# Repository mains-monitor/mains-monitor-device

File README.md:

# Mains Monitor

The device monitors a presence of mains voltage and sends notifications to the Backend when it turns on or off.
It uses ESP32-C3 MCU as a core component. It implements the logic of the device and connects it to the outer world via Wi-Fi.

The device powers from 5V DC via micro-USB connector and from 3.7V 1000 mAh Li-Po battery, when mains is not available.
Most of the time the device stays in deep sleep mode, so it consumes micro Amps. It wakes up for 20 sec when 5V DC power source becomes available or turns off just for sending a notification to the Backend, then goes to deep sleep again. Peak power consumption when device is transmitting data via Wi-Fi is 500 mA.

# First launch configuration

When device starts the first time it creates a Wi-Fi hotspot network with SSID ``MD_<CHIPID>``. The password is ``md123456``.
Connect to it from a smartphone. After that it will open a configuration portal powered by WiFiManager Arduino library. It allows you to select a home Wi-Fi network the device will be connected to and a DTEK group number. The DTEK group number will be used later on the Backend.

# Folders & files description

* ``cad/`` - FreeCAD project and *.STL files of the enclosure for 3D printing
* ``libs/`` - KiCAD library files (schematic symbols and footprints)
* ``production/`` - Gerber, component placement files and Bill Of Materials for PCB production on the factory (for example, JLCPCB)
* ``firmware/`` - firmware sources for ESP32-C3 MCU, the heart of Mains Monitor

# Schematic

## PCB design

See [PDF file](doc/pcb-design.pdf) or ``./mains-detector.kicad_pcb`` filer in KiCAD format.

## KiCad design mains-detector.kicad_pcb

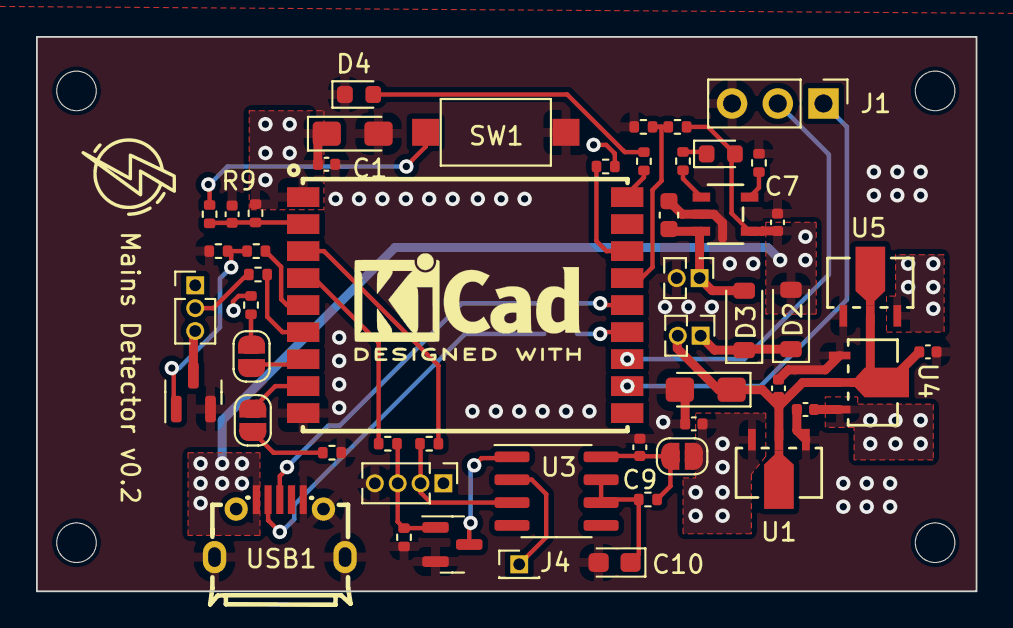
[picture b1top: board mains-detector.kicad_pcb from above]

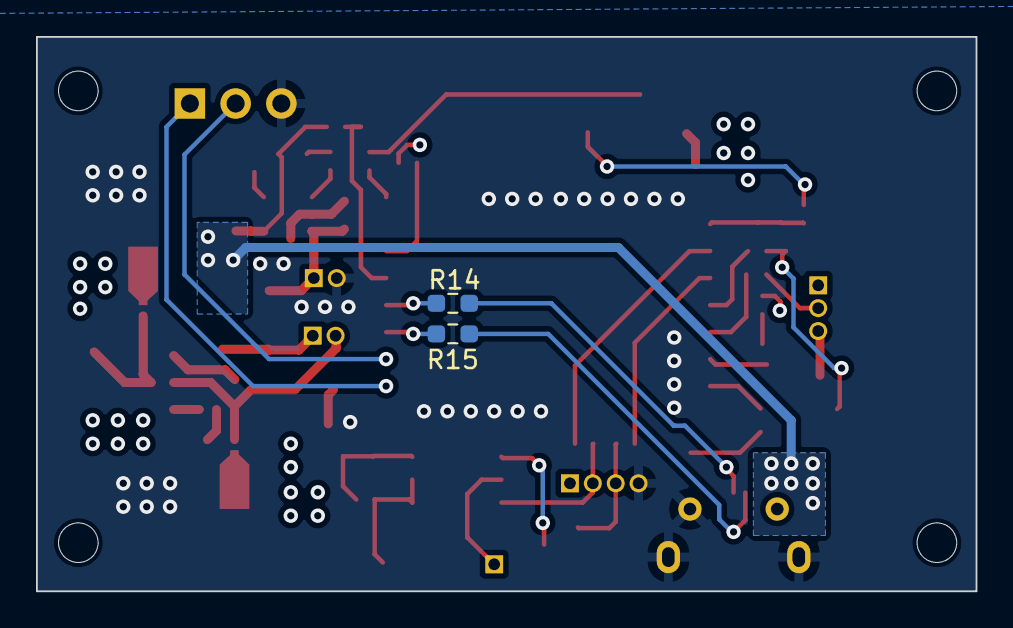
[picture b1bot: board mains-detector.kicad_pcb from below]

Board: 4 copper layers, 52.2 x 30.8 mm, 58 parts (2 on the bottom side), 38 nets.

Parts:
BT1: Li-Po 3.7V; PinHeader_1x02_P1.27mm_Vertical
C1, C9: 0.1u; C_0402_1005Metric
C2, C4: 10u; CP_EIA-3216-10_Kemet-I_Pad1.58x1.35mm_HandSolder
C3: 100n; C_0402_1005Metric
C5, C6, C7, C11, C12: 1u; C_0402_1005Metric
C8: 10u; C_0603_1608Metric
C10: 4.7u; CP_EIA-2012-12_Kemet-R
D1: LED-Blue; LED_0603_1608Metric
D2, D3: MBR0520LT1; D_SOD-123
D4: STATUS; LED_0603_1608Metric
H1, H2, H3, H4: MountingHole; MountingHole_2.2mm_M2
J1: UART; PinHeader_1x03_P2.54mm_Vertical
J2: FS1000A; PinHeader_1x03_P1.27mm_Vertical
J3: GPIOS; PinHeader_1x04_P1.27mm_Vertical
J4: ANT; PinHeader_1x01_P1.27mm_Vertical
JP1, JP2, JP3: SolderJumper_2_Open; SolderJumper-2_P1.3mm_Open_RoundedPad1.0x1.5mm
L1: ESP-C3-13U-4M; WIRELM-SMD_ESP-C3-13U-2M
Q1, Q2: IRLML2402; SOT-23
R1, R2, R3, R7, R9: 10k; R_0402_1005Metric
R4, R8: 3k; R_0402_1005Metric
R5, R6: 5k; R_0402_1005Metric
R10, R11, R12, R18, R19: 100; R_0402_1005Metric
R13, R16, R17: 100k; R_0402_1005Metric
R14, R15: 22; R_0603_1608Metric_Pad0.98x0.95mm_HandSolder
SW1: RESET; SW_SPST_CK_RS282G05A3
SW2: ONOFF; PinHeader_1x02_P1.27mm_Vertical
U1, U4, U5: XC6206P332PR-G; SOT-89_TOR
U2: TP4065-4.2V-SOT25-R; SOT-23-5L_TPW
U3: NE555D; SOIC-8_3.9x4.9mm_P1.27mm
USB1: MICROXNJ; MICRO-USB-SMD_MICROXNJ

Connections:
D+: L1.14 (IO19), R14.2
D-: L1.13 (IO18), R15.2
EN: C3.1, L1.2 (EN), R9.2, R10.1
GND: BT1.2 (-), C1.1, C2.2, C3.2, C4.2, C5.2, C6.2, C7.2, C8.2, C9.1, C10.2, C11.2, C12.2, D4.1 (K), J1.3, J3.4, L1.9 (GND), Q1.2 (S), Q2.2 (S), R2.2, R5.2, R7.2, R13.1, R16.1, SW1.1, U1.1 (VSS), U2.2 (GND), U4.1 (VSS), U5.1 (VSS), USB1.5 (GND), USB1.6 (SH1), USB1.7 (SH2), USB1.8 (SH3), USB1.9 (SH4)
IO4: J3.2, R18.1, U3.3 (Q)
IO5: J3.3, Q1.1 (G), R16.2, R19.1
unnamed: BT1.1 (+), C8.1, D3.2 (A), U2.3 (BAT)
unnamed: D1.1 (K), R4.2
unnamed: D2.1 (K), D3.1 (K), SW2.1 (A)
unnamed: D4.2 (A), R8.1
unnamed: J1.1, L1.11 (RXD)
unnamed: J1.2, L1.12 (TXD)
unnamed: J2.2, R11.2
unnamed: J2.3, Q2.3 (D)
unnamed: J4.1, U3.2 (TR)
unnamed: JP1.1 (A), R3.2
unnamed: JP1.2 (B), L1.7 (IO8)
unnamed: JP2.1 (A), R2.1
unnamed: JP2.2 (B), L1.8 (IO9)
unnamed: C9.2, JP3.1 (A), R17.2, U3.8 (VCC)
unnamed: L1.18 (IO0), R8.2
unnamed: L1.16 (IO2), R1.2
unnamed: L1.3 (IO4), R18.2
unnamed: L1.4 (IO5), R19.2
unnamed: Q1.3 (D), U3.1 (GND)
unnamed: Q2.1 (G), R12.2, R13.2
unnamed: R10.2, SW1.2
unnamed: C4.1, C5.1, C11.1, SW2.2 (B), U1.2 (VIN), U4.2 (VIN), U5.2 (VIN)
unnamed: R4.1, U2.1 (CHRG)
unnamed: R5.1, U2.5 (PROG)
unnamed: C10.1, R17.1, U3.6 (THR), U3.7 (DIS)
unnamed: R14.1, USB1.3 (D+)
unnamed: R15.1, USB1.2 (D-)
SENSE: L1.15 (IO3), R6.2, R7.1
TX: L1.6 (IO7), R11.1
TX_EN: L1.5 (IO6), R12.1
VBUS: C7.1, D1.2 (A), D2.2 (A), R6.1, U2.4 (VCC), USB1.1 (VBUS)
VCC: C1.2, C2.1, C6.1, C12.1, J2.1, J3.1, JP3.2 (B), L1.1 (VCC), R1.1, R3.1, R9.1, U1.3 (VOUT), U4.3 (VOUT), U5.3 (VOUT)

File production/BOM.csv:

"Comment","Designator","Footprint","LCSC"
"0.1u","C1,C9","Capacitor_SMD:C_0402_1005Metric","C307331"
"10u","C2,C4","Capacitor_Tantalum_SMD:CP_EIA-3216-10_Kemet-I_Pad1.58x1.35mm_HandSolder","C7171"
"100n","C3","Capacitor_SMD:C_0402_1005Metric","C307331"
"1u","C5,C6,C7,C11,C12","Capacitor_SMD:C_0402_1005Metric","C52923"
"10u","C8","Capacitor_SMD:C_0603_1608Metric","C96446"
"4.7u","C10","Capacitor_Tantalum_SMD:CP_EIA-2012-12_Kemet-R","C2158112"
"LED-Blue","D1","LED_SMD:LED_0603_1608Metric","C2286"
"MBR0520LT1","D2,D3","Diode_SMD:D_SOD-123","C8598"
"STATUS","D4","LED_SMD:LED_0603_1608Metric","C2290"
"IRLML2402","Q1,Q2","Package_TO_SOT_SMD:SOT-23","C20917"
"10k","R1,R2,R3,R7,R9","Resistor_SMD:R_0402_1005Metric","C25744"
"3k","R4,R8","Resistor_SMD:R_0402_1005Metric","C25784"
"5k","R5,R6","Resistor_SMD:R_0402_1005Metric","C25905"
"100","R10,R11,R12,R18,R19","Resistor_SMD:R_0402_1005Metric","C25076"
"100k","R13,R16,R17","Resistor_SMD:R_0402_1005Metric","C25741"
"XC6206P332PR-G","U1,U4,U5","footprints:SOT-89_TOR","C526275"
"TP4065-4.2V-SOT25-R","U2","footprints1:SOT-23-5L_TPW","C113540"
"NE555D","U3","Package_SO:SOIC-8_3.9x4.9mm_P1.27mm","C356725"
"MICROXNJ","USB1","kicad_lceda:MICRO-USB-SMD_MICROXNJ","C404969"

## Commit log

2024-04-07 Update CAD and documentation files
2024-04-13 Fix schematic / pcb design gaps, update enclosure
2024-06-21 feat: Add FreeRTOS firmware files and configurations for ESP32-C3
